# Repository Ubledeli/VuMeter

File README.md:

based on:

[VU Meter](http://sound.whsites.net/project55.htm "ESP project 55")

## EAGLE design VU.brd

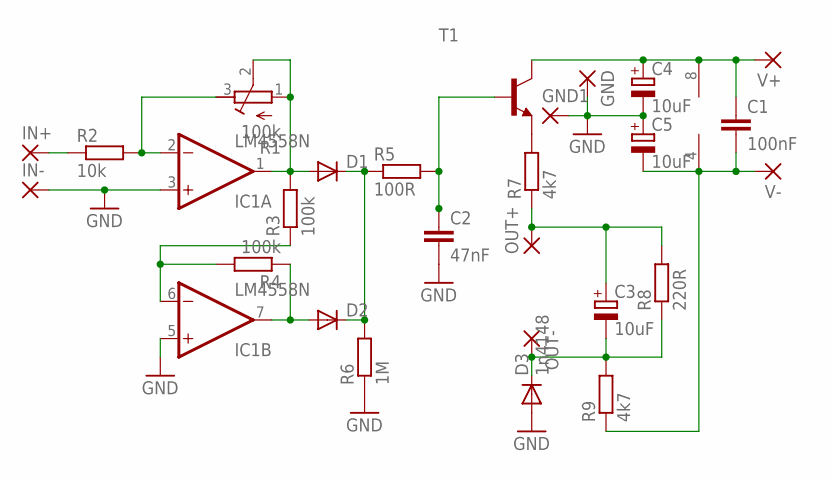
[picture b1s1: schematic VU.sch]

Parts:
C1: 100nF; C050-025X075
C2: 47nF; C050-025X075
C3, C4, C5: 10uF; E2,5-5
D1, D2: DIODE-D-5; D-5
D3: 1n4148; D-5
GND, GND1: WIREPAD1,6/0,8; 1,6/0,8
IC1: LM4558N; DIL08
IN+: WIREPAD1,6/0,8; 1,6/0,8
IN-: WIREPAD1,6/0,8; 1,6/0,8
OUT+: WIREPAD1,6/0,8; 1,6/0,8
OUT-: WIREPAD1,6/0,8; 1,6/0,8
R1: 100k; RTRIM64X
R2: 10k; 0207/7
R3: 100k; 0207/7
R4: 100k; 0207/2V
R5: 100R; 0207/7
R6: 1M; 0207/7
R7, R9: 4k7; 0207/7
R8: 220R; 0207/7
T1: BC546-NPN-TO92-CBE; TO92-CBE
V+: WIREPAD1,6/0,8; 1,6/0,8
V-: WIREPAD1,6/0,8; 1,6/0,8

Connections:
GND: C2.2, C4.-, C5.+, D3.A, GND.1, GND1.1, IC1.3 (+IN), IC1.5 (+IN), IN-.1, R6.1
unnamed: IN+.1, R2.1
unnamed: IC1.2 (-IN), R1.3 (E), R2.2
unnamed: D1.A, IC1.1 (OUT), R1.1 (A), R1.2 (S), R3.2
unnamed: IC1.6 (-IN), R3.1, R4.2
unnamed: D2.A, IC1.7 (OUT), R4.1
unnamed: D1.C, D2.C, R5.1, R6.2
unnamed: C2.1, R5.2, T1.B
unnamed: R7.2, T1.E
unnamed: C3.+, OUT+.1, R7.1, R8.2
unnamed: C3.-, D3.C, OUT-.1, R8.1, R9.2
unnamed: C1.2, C5.-, IC1.4 (V-), R9.1, V-.1
unnamed: C1.1, C4.+, IC1.8 (V+), T1.C, V+.1

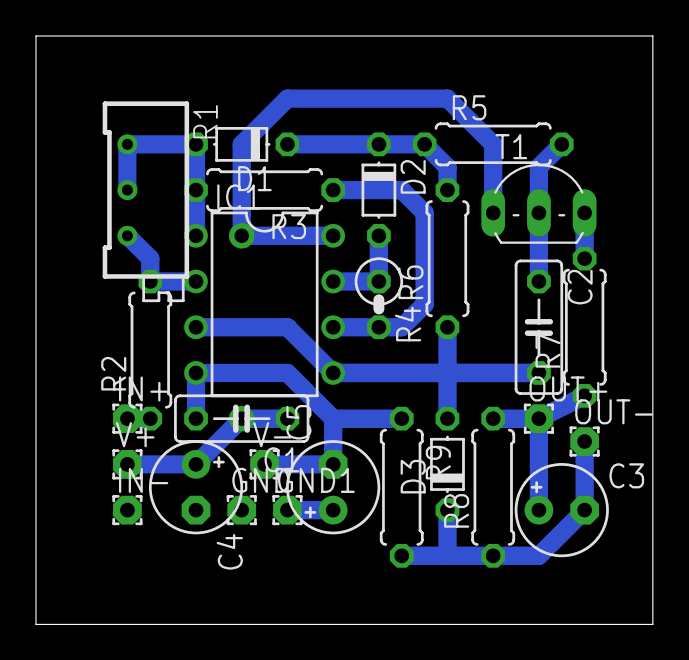
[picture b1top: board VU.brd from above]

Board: 2 copper layers, 34.3 x 32.7 mm, 27 parts (0 on the bottom side), 13 nets.

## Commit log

2017-05-16 link
